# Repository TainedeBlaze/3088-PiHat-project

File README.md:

# 3088-PiHat-project
# Taine de Buys
# 2021/05/12

brief description of what our PiHat does: 
We have designed a temperature sensor piHat, that will be able to measure the temperature of anything from a liquid to the ambient room temperature, and convey this temperature through a set out LED outputs. Each LED can be configured to turn on for when the temperature surpasses a designated threshold. This is done through a comparator op amp configuration and potentiometers for each LED. The circuit has 3 subsysetms, a voltage regulator that sets the voltage going into the LEDs, the temperature sensor itself, and the output LEDs which also have a status LED that shows whether the piHat is recieving power. 

Edits have now been made in a seperate branch to prove i know whats cracking

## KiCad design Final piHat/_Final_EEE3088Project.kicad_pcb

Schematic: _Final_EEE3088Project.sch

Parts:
Buck/Boost1: LTC3442; DFN-12-1EP_3x4mm_P0.5mm_EP1.7x3.3mm
C1: 0.001u; CP_Radial_D4.0mm_P1.50mm
C2: 10u; CP_Radial_D4.0mm_P1.50mm
C3: 470p; CP_Radial_D4.0mm_P1.50mm
C4: 0.01u; CP_Radial_D4.0mm_P1.50mm
C5: 220p; CP_Radial_D4.0mm_P1.50mm
C6: 22u; CP_Radial_D4.0mm_P1.50mm
D1: DIODE; D_DO-15_P2.54mm_Vertical_AnodeUp
D2, D3: DIODE; D_A-405_P2.54mm_Vertical_AnodeUp
H1, H2, H3, H4: MountingHole; MountingHole_2.7mm
J1: Conn_02x20_Odd_Even; PinHeader_2x20_P2.00mm_Vertical
L1: 4.7u; L_Axial_L5.3mm_D2.2mm_P2.54mm_Vertical_Vishay_IM-1
LED1, LED2, LED3: LED; LED_D1.8mm_W1.8mm_H2.4mm_Horizontal_O1.27mm_Z1.6mm
OP1, OP2, OP3: OP07; TO-5-8
R1: 1M; R_Axial_DIN0204_L3.6mm_D1.6mm_P1.90mm_Vertical
R2: 71.5k; R_Axial_DIN0204_L3.6mm_D1.6mm_P1.90mm_Vertical
R3, R8, R10, R16: 1k; R_Axial_DIN0204_L3.6mm_D1.6mm_P1.90mm_Vertical
R4: 200k; R_Axial_DIN0204_L3.6mm_D1.6mm_P5.08mm_Horizontal
R5: 15k; R_Axial_DIN0204_L3.6mm_D1.6mm_P5.08mm_Horizontal
R6: 340k; R_Axial_DIN0204_L3.6mm_D1.6mm_P5.08mm_Horizontal
R7: 135k; R_Axial_DIN0204_L3.6mm_D1.6mm_P5.08mm_Horizontal
R9: 2.2k; R_Axial_DIN0204_L3.6mm_D1.6mm_P1.90mm_Vertical
R11: 24.2k; R_Axial_DIN0204_L3.6mm_D1.6mm_P1.90mm_Vertical
R12, R15: 10k; R_Axial_DIN0204_L3.6mm_D1.6mm_P5.08mm_Horizontal
R13: 1k; R_Axial_DIN0204_L3.6mm_D1.6mm_P5.08mm_Horizontal
R14: 21.71k; R_Axial_DIN0204_L3.6mm_D1.6mm_P5.08mm_Horizontal
R17: 19.53k; R_Axial_DIN0204_L3.6mm_D1.6mm_P1.90mm_Vertical
R18: 10k; R_Axial_DIN0204_L3.6mm_D1.6mm_P1.90mm_Vertical
TMP1: LM135; SHT1x

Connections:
/Vreg: Buck/Boost1.8 (VOUT), C6.1, R3.1, R6.1, R9.1, R11.1, R14.1, R17.1
/Vtemp: R8.2
GND: Buck/Boost1.3 (SGND), Buck/Boost1.5 (PGND), Buck/Boost1.10 (RLIM), Buck/Boost1.13 (PADGND), C1.2, C2.2, C4.2, C6.2, J1.6, OP1.1 (VOS), OP1.4 (V-), OP1.8 (VOS), OP2.1 (VOS), OP2.4 (V-), OP2.8 (VOS), OP3.1 (VOS), OP3.4 (V-), OP3.8 (VOS), R2.2, R4.2, R7.2, R10.2, R12.2, R13.2, R15.2, R16.2, R18.2, TMP1.3
unnamed: Buck/Boost1.1 (~SHDN~/SS), C1.1, R1.2
unnamed: Buck/Boost1.2 (RT), R2.1
unnamed: Buck/Boost1.4 (SW1), L1.1
unnamed: Buck/Boost1.6 (SW2), L1.2
unnamed: Buck/Boost1.7 (BURST), C4.1, R4.1
unnamed: Buck/Boost1.11 (VC), R5.2
unnamed: Buck/Boost1.12 (FB), C3.1, C5.2, R6.2, R7.1
unnamed: C3.2, R5.1
unnamed: C5.1, R9.2
unnamed: D1.1 (K), OP1.6
unnamed: D1.2 (A), LED1.2 (A)
unnamed: D2.1 (K), OP2.6
unnamed: D2.2 (A), LED2.2 (A)
unnamed: D3.1 (K), OP3.6
unnamed: D3.2 (A), LED3.2 (A)
unnamed: LED1.1 (K), R10.1
unnamed: LED2.1 (K), R13.1
unnamed: LED3.1 (K), R16.1
unnamed: OP1.2 (-), R11.2, R12.1
unnamed: OP1.3 (+), OP2.3 (+), OP3.3 (+), R8.1
unnamed: OP2.2 (-), R14.2, R15.1
unnamed: OP3.2 (-), R17.2, R18.1
unnamed: R3.2, TMP1.1
Vin: Buck/Boost1.9 (VIN), C2.1, J1.1, OP1.7 (V+), OP2.7 (V+), OP3.7 (V+), R1.1

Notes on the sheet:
David Da Costa-DCSDAV001 Micheal Altschuler_ALTMIC003 Tain De Buys-DBYTAI001
PiHat Schematic
02/06/2021
Rasberry Pi Mounting Holes
Rasberry Pi GPIO Headers

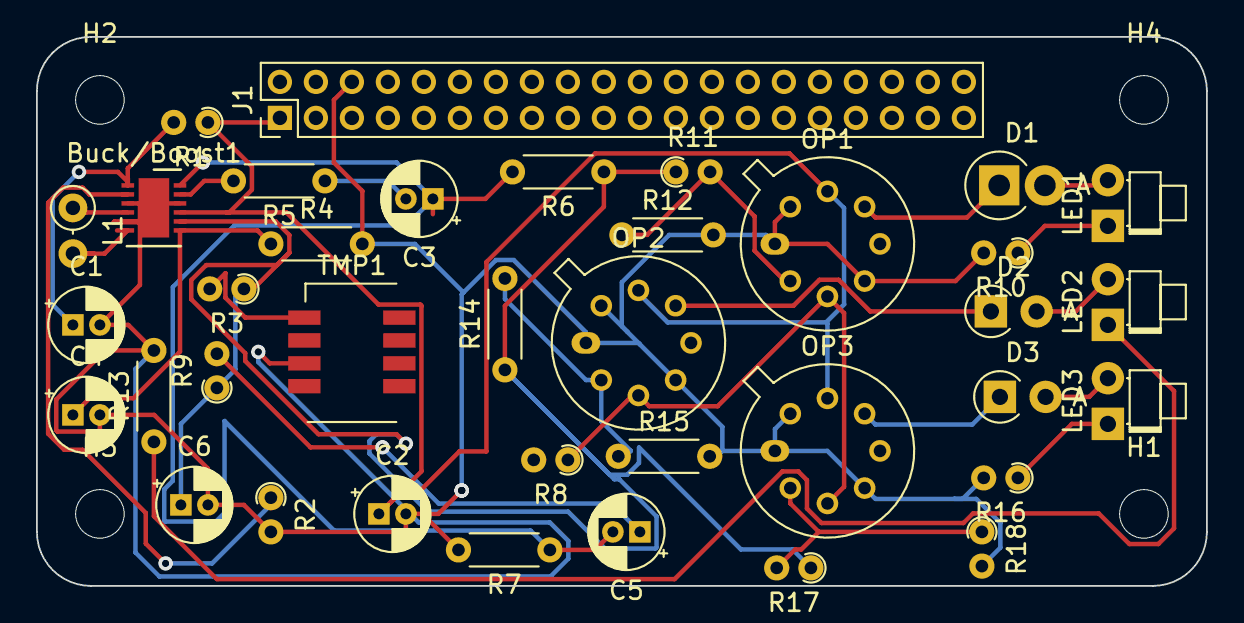
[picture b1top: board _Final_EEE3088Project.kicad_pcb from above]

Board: 2 copper layers, 65.0 x 30.5 mm, 41 parts (0 on the bottom side), 26 nets.

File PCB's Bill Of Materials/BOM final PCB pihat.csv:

"Id";"Designator";"Package";"Quantity";"Designation";"Supplier and ref";
1;"R17";"R_Axial_DIN0204_L3.6mm_D1.6mm_P1.90mm_Vertical";1;"19.53k";;;
2;"R5";"R_Axial_DIN0204_L3.6mm_D1.6mm_P5.08mm_Horizontal";1;"15k";;;
3;"R4";"R_Axial_DIN0204_L3.6mm_D1.6mm_P5.08mm_Horizontal";1;"200k";;;
4;"Buck/Boost1";"DFN-12-1EP_3x4mm_P0.5mm_EP1.7x3.3mm";1;"LTC3442";;;
5;"C1";"CP_Radial_D4.0mm_P1.50mm";1;"0.001u";;;
6;"C2";"CP_Radial_D4.0mm_P1.50mm";1;"10u";;;
7;"C3";"CP_Radial_D4.0mm_P1.50mm";1;"470p";;;
8;"C4";"CP_Radial_D4.0mm_P1.50mm";1;"0.01u";;;
9;"C5";"CP_Radial_D4.0mm_P1.50mm";1;"220p";;;
10;"C6";"CP_Radial_D4.0mm_P1.50mm";1;"22u";;;
11;"D1";"D_DO-15_P2.54mm_Vertical_AnodeUp";1;"DIODE";;;
12;"D2,D3";"D_A-405_P2.54mm_Vertical_AnodeUp";2;"DIODE";;;
13;"H1,H2,H3,H4";"MountingHole_2.7mm";4;"MountingHole";;;
14;"J1";"PinHeader_2x20_P2.00mm_Vertical";1;"Conn_02x20_Odd_Even";;;
15;"L1";"L_Axial_L5.3mm_D2.2mm_P2.54mm_Vertical_Vishay_IM-1";1;"4.7u";;;
16;"LED1,LED2,LED3";"LED_D1.8mm_W1.8mm_H2.4mm_Horizontal_O1.27mm_Z1.6mm";3;"LED";;;
17;"OP1,OP2,OP3";"TO-5-8";3;"OP07";;;
18;"R1";"R_Axial_DIN0204_L3.6mm_D1.6mm_P1.90mm_Vertical";1;"1M";;;
19;"R2";"R_Axial_DIN0204_L3.6mm_D1.6mm_P1.90mm_Vertical";1;"71.5k";;;
20;"R3,R8,R10,R16";"R_Axial_DIN0204_L3.6mm_D1.6mm_P1.90mm_Vertical";4;"1k";;;
21;"R6";"R_Axial_DIN0204_L3.6mm_D1.6mm_P5.08mm_Horizontal";1;"340k";;;
22;"R7";"R_Axial_DIN0204_L3.6mm_D1.6mm_P5.08mm_Horizontal";1;"135k";;;
23;"R9";"R_Axial_DIN0204_L3.6mm_D1.6mm_P1.90mm_Vertical";1;"2.2k";;;
24;"R11";"R_Axial_DIN0204_L3.6mm_D1.6mm_P1.90mm_Vertical";1;"24.2k";;;
25;"R12,R15";"R_Axial_DIN0204_L3.6mm_D1.6mm_P5.08mm_Horizontal";2;"10k";;;
26;"R13";"R_Axial_DIN0204_L3.6mm_D1.6mm_P5.08mm_Horizontal";1;"1k";;;
27;"R14";"R_Axial_DIN0204_L3.6mm_D1.6mm_P5.08mm_Horizontal";1;"21.71k";;;
28;"R18";"R_Axial_DIN0204_L3.6mm_D1.6mm_P1.90mm_Vertical";1;"10k";;;
29;"TMP1";"SHT1x";1;"LM135";;;

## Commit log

2021-05-12 First commit with readme completed
2021-05-12 Final commit for assignment with new READme
2021-06-03 Added Files via Upload
    Added the complete PiHat KiCad Circuit W/O Submodules
    Use these uploads to make PCB
2021-06-04 All subsystems
2021-06-04 Update README.md
    Brief description of Comparator-LED subsystem.
2021-06-04 Create README.md
    Brief description of LM135 temperature sensor subsystem.
2021-06-04 Files for the PCB design and GBR
2021-06-04 Create README.md
    Brief description of buck-boost regulator subsystem.
2021-06-04 Add files via upload
    All subsystem files.
2021-06-04 Create README.md
    Brief description of Comparator-LED subsystem
2021-06-04 Create README.md
    Brief description of LM135 temperature sensor subsystem
2021-06-11 Add files via upload
    Correct PCB file uploaded
2021-06-11 Delete EEE3088 PCB Kicad.kicad_pcb
    Deleted dummy PCB
2021-06-11 Add files via upload
    KiCad Schematic re-uploaded into a single file
2021-06-11 Add files via upload
    Screenshot of LTC3442 simulation.
2021-06-11 Add files via upload
    Added bill of materials
2021-06-11 Add files via upload
    KiCad schematic screenshot of LTC3442.
2021-06-11 Add files via upload
    Simulations of Comparator-LED subsystem for T = 2 degrees, T = 26 degrees, T = 52 degrees [Celcius].
2021-06-11 Add files via upload
    KiCad schematic of the Comparator-LED subsystem.
2021-06-11 Add files via upload
    Added Centroid files
2021-06-11 Add files via upload
    Added how to on manufacturing your own PCB
2021-06-11 Add files via upload
    LM135 (TMP135) output simulation.
2021-06-11 Add files via upload
    added top pick and place
2021-06-11 Create GettingStarted.md
    Added how to use Pihat
2021-06-11 Add files via upload
    KiCad schematic for the LM135 temperature sensor submodule.
2021-06-11 Add files via upload
    Screenshots of both the 2D and 3D PCB's.
2021-06-17 Final PiHat KiCad
2021-06-17 Add files via upload
    Assignment 4 word document/report.
2021-06-17 Delete PCB and Gerber Files directory
    Deleted V1
2021-06-17 Create Pick and place files
2021-06-18 LM135 library.
